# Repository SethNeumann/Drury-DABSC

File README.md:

# REPO NAME: Drury-DABSC
## License: Creative Commons Attribution-NonCommercial-ShareAlike

Dennis Drury designed the Dual ABS Controller (DABSC) as a simple solution for ABS.  
  
The Dual ABS Signal Controller provides a simple, no software, solution for the modeler looking for a prototypical Automatic Block Signaling (ABS) system.
This board provides signal control for two blocks of 3 aspect (Green - Yellow - Red) route signaling for two blocks.  
The Dual ABS Signal Controller can be used in either single track (1 segment for each signaled direction) or double track (Rule 251, Current of Traffic)
applications.

This is an excellent product for modular and sectional railroads as well as permanent applications.  We recommend our cpOD (screw terminal option) detector
for detection input. The Dual ABS Signal Controller is NOT MSS compatible.

This board is designed and supported by Dennis Drury, a former Southern Pacific Signal Maintainer and the design has given him good service for 30 years!
See Dennis' clinic from the 2017 PCR Convention on the development of this board on the www.modelrailroadcontrolsystems.com sitte under Simple Signaling 
and accessories

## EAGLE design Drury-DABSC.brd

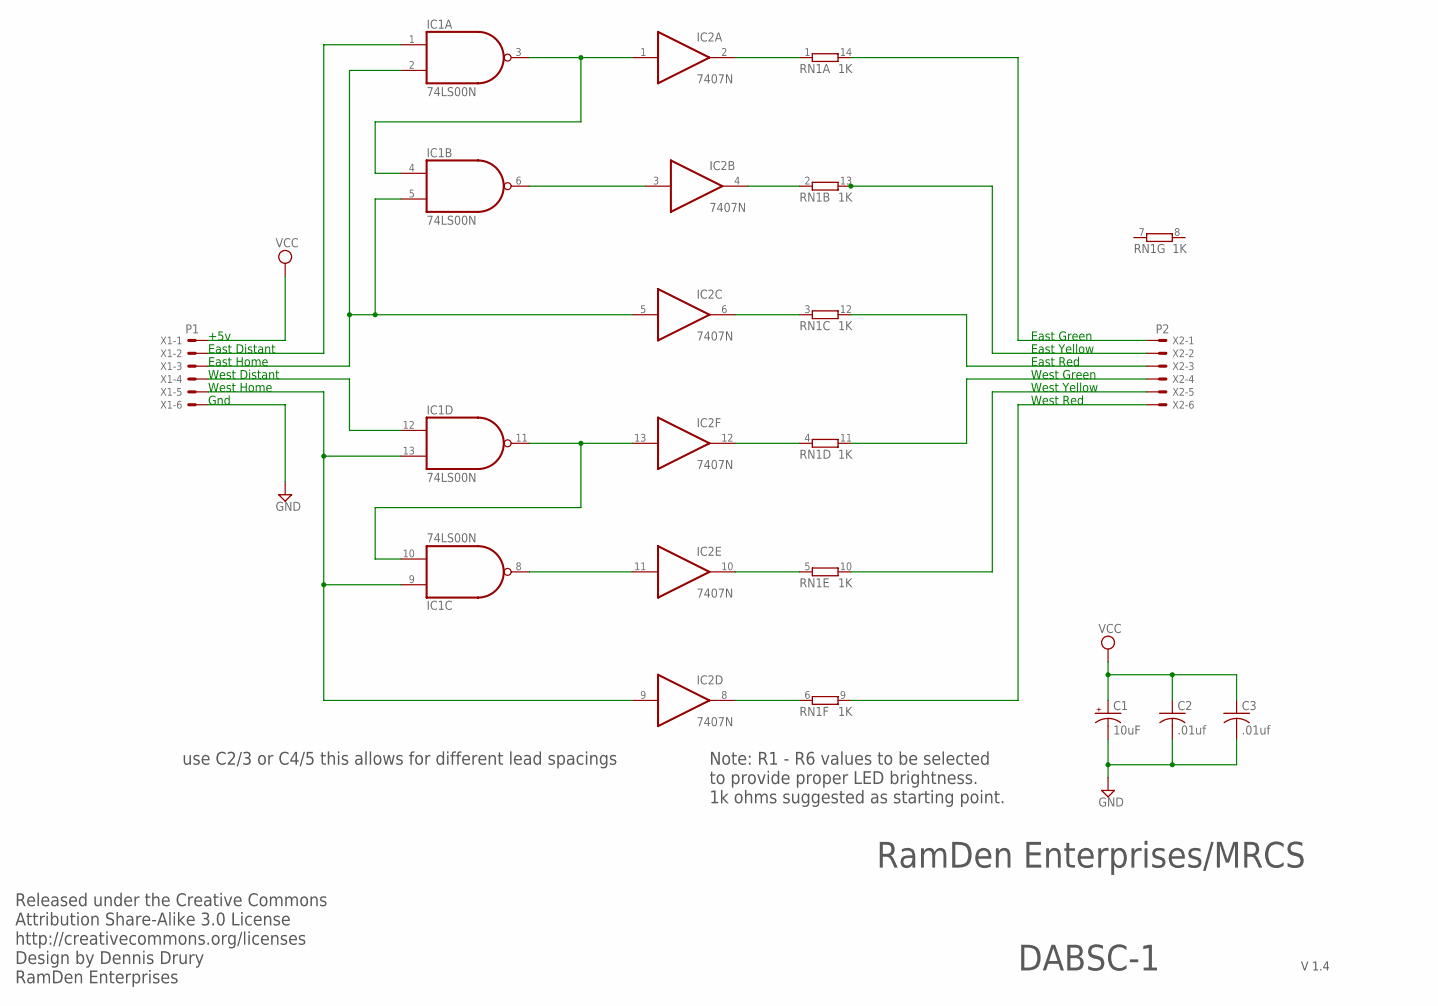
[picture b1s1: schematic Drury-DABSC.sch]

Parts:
C1: 10uF; E2-5
C2, C3: .01uf; C050-025X075
IC1: 74LS00N; DIL14
IC2: 7407N; DIL14
RN1: 1K; DIL14
X1: P1; 22-23-2061
X2: P2; 22-23-2061

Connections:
GND: C1.-, C2.2, C3.2, IC1.7 (GND), IC2.7 (GND), X1.6
unnamed: IC1.3 (O), IC1.4 (I0), IC2.1 (I)
unnamed: IC1.6 (O), IC2.3 (I)
unnamed: IC2.2 (O), RN1.1
unnamed: IC1.8 (O), IC2.11 (I)
unnamed: IC2.4 (O), RN1.2 (1)
unnamed: IC1.10 (I1), IC1.11 (O), IC2.13 (I)
unnamed: IC2.6 (O), RN1.3 (1)
unnamed: RN1.14 (2), X2.1
unnamed: RN1.13 (2), X2.2
unnamed: IC1.1 (I0), X1.2
unnamed: IC1.2 (I1), IC1.5 (I1), IC2.5 (I), X1.3
unnamed: RN1.12 (2), X2.3
unnamed: IC2.12 (O), RN1.4 (1)
unnamed: IC2.10 (O), RN1.5 (1)
unnamed: IC2.8 (O), RN1.6 (1)
unnamed: RN1.9 (2), X2.6
unnamed: RN1.10 (2), X2.5
unnamed: IC1.12 (I0), X1.4
unnamed: RN1.11 (2), X2.4
unnamed: IC1.9 (I0), IC1.13 (I1), IC2.9 (I), X1.5
VCC: C1.+, C2.1, C3.1, IC1.14 (VCC), IC2.14 (VCC), X1.1

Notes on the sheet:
RamDen Enterprises/MRCS
V 1.4
DABSC-1
East Distant
East Home
West Home
West Distant
East Green
East Yellow
East Red
West Green
West Yellow
West Red
Released under the Creative Commons Attribution Share-Alike 3.0 License http://creativecommons.org/licenses Design by Dennis Drury RamDen Enterprises
Note: R1 - R6 values to be selected to provide proper LED brightness. 1k ohms suggested as starting point.
+5v
Gnd
use C2/3 or C4/5 this allows for different lead spacings

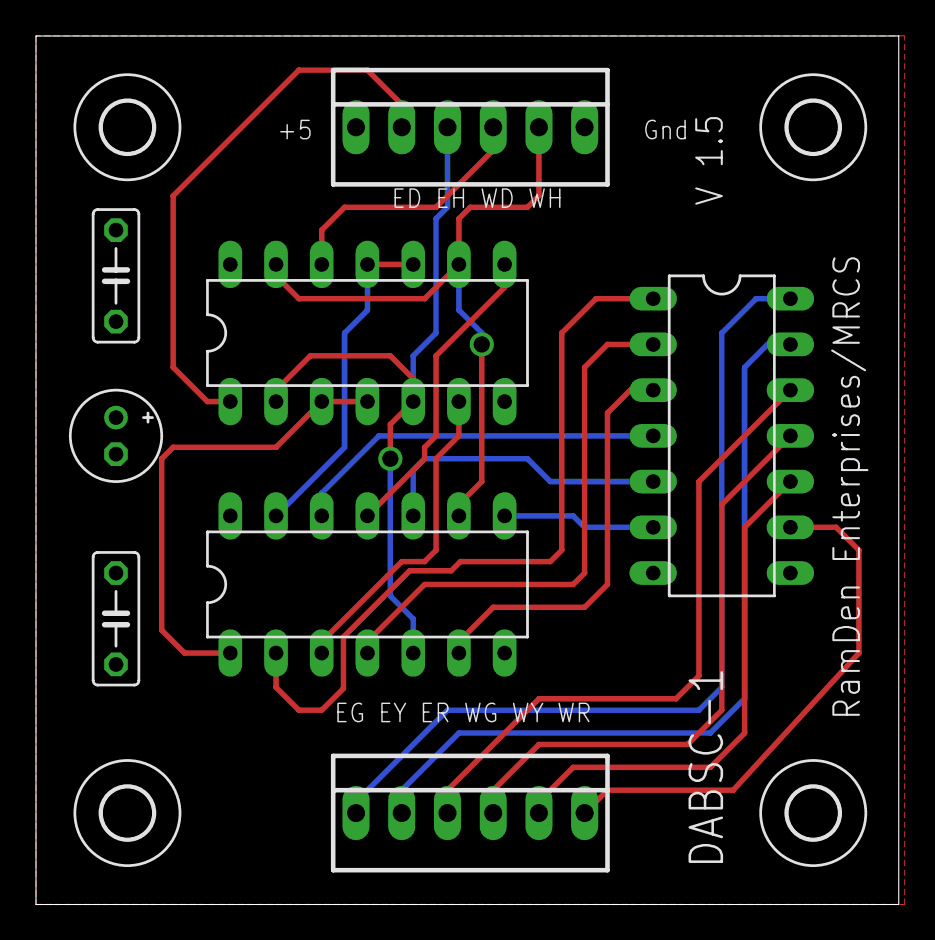
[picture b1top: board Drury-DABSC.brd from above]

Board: 2 copper layers, 47.9 x 48.2 mm, 14 parts (0 on the bottom side), 22 nets.

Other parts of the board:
U$1, U$2, U$3, U$4: 2,8
U$5: MRCSLOGOTOP
U$6: CA-PROP65WARNING

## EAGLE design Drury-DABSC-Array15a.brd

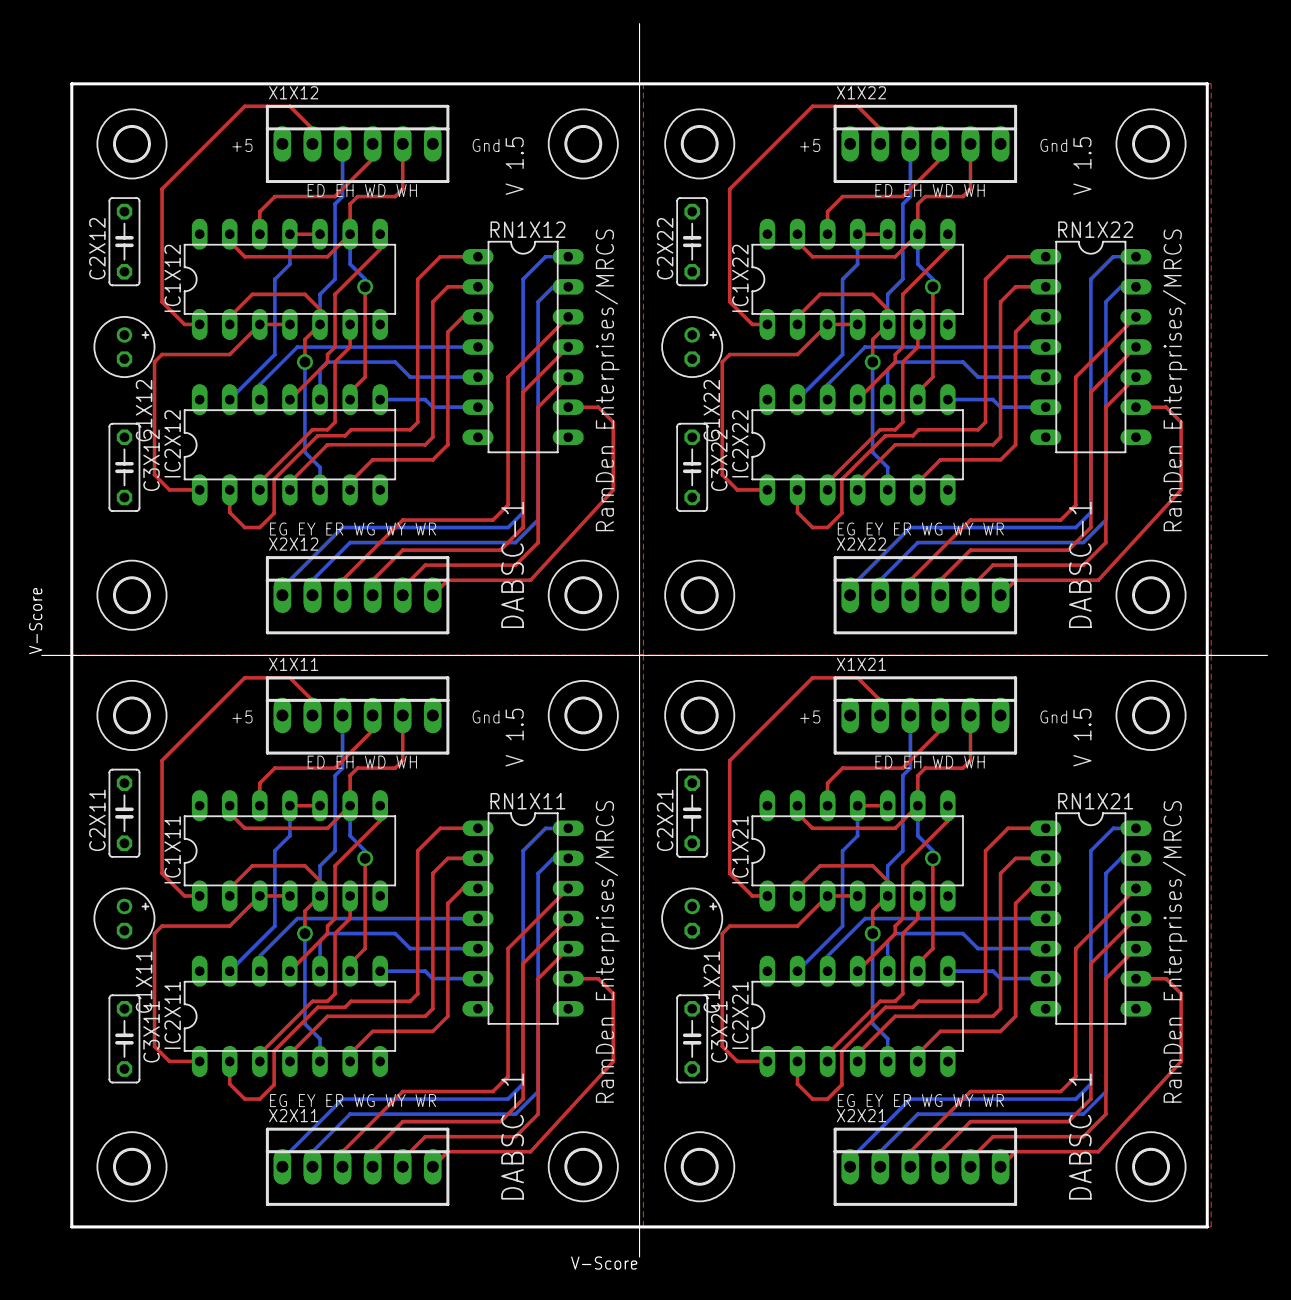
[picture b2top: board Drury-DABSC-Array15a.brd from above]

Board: 2 copper layers, 103.5 x 104.1 mm, 56 parts (0 on the bottom side), 88 nets.

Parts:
C1X11, C1X12, C1X21, C1X22: 10uF; E2-5
C2X11, C2X12, C2X21, C2X22, C3X11, C3X12, C3X21, C3X22: .01uf; C050-025X075
IC1X11, IC1X12, IC1X21, IC1X22: 74LS00N; DIL14
IC2X11, IC2X12, IC2X21, IC2X22: 7407N; DIL14
RN1X11, RN1X12, RN1X21, RN1X22: 1K; DIL14
U$1X11, U$1X12, U$1X21, U$1X22, U$2X11, U$2X12, U$2X21, U$2X22, U$3X11, U$3X12, U$3X21, U$3X22, U$4X11, U$4X12, U$4X21, U$4X22: 2,8
U$5X11, U$5X12, U$5X21, U$5X22: MRCSLOGOTOP
U$6X11, U$6X12, U$6X21, U$6X22: CA-PROP65WARNING
X1X11, X1X12, X1X21, X1X22: P1; 22-23-2061
X2X11, X2X12, X2X21, X2X22: P2; 22-23-2061

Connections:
GNDX11: C1X11.-, C2X11.2, C3X11.2, IC1X11.7, IC2X11.7, X1X11.6
GNDX12: C1X12.-, C2X12.2, C3X12.2, IC1X12.7, IC2X12.7, X1X12.6
GNDX21: C1X21.-, C2X21.2, C3X21.2, IC1X21.7, IC2X21.7, X1X21.6
GNDX22: C1X22.-, C2X22.2, C3X22.2, IC1X22.7, IC2X22.7, X1X22.6
unnamed: IC1X11.3, IC1X11.4, IC2X11.1
unnamed: IC1X12.3, IC1X12.4, IC2X12.1
unnamed: IC1X21.3, IC1X21.4, IC2X21.1
unnamed: IC1X22.3, IC1X22.4, IC2X22.1
unnamed: IC1X11.6, IC2X11.3
unnamed: IC1X12.6, IC2X12.3
unnamed: IC1X21.6, IC2X21.3
unnamed: IC1X22.6, IC2X22.3
unnamed: IC2X11.2, RN1X11.1
unnamed: IC2X12.2, RN1X12.1
unnamed: IC2X21.2, RN1X21.1
unnamed: IC2X22.2, RN1X22.1
unnamed: IC1X11.8, IC2X11.11
unnamed: IC1X12.8, IC2X12.11
unnamed: IC1X21.8, IC2X21.11
unnamed: IC1X22.8, IC2X22.11
unnamed: IC2X11.4, RN1X11.2
unnamed: IC2X12.4, RN1X12.2
unnamed: IC2X21.4, RN1X21.2
unnamed: IC2X22.4, RN1X22.2
unnamed: IC1X11.10, IC1X11.11, IC2X11.13
unnamed: IC1X12.10, IC1X12.11, IC2X12.13
unnamed: IC1X21.10, IC1X21.11, IC2X21.13
unnamed: IC1X22.10, IC1X22.11, IC2X22.13
unnamed: IC2X11.6, RN1X11.3
unnamed: IC2X12.6, RN1X12.3
unnamed: IC2X21.6, RN1X21.3
unnamed: IC2X22.6, RN1X22.3
unnamed: RN1X11.14, X2X11.1
unnamed: RN1X12.14, X2X12.1
unnamed: RN1X21.14, X2X21.1
unnamed: RN1X22.14, X2X22.1
unnamed: RN1X11.13, X2X11.2
unnamed: RN1X12.13, X2X12.2
unnamed: RN1X21.13, X2X21.2
unnamed: RN1X22.13, X2X22.2
unnamed: IC1X11.1, X1X11.2
unnamed: IC1X12.1, X1X12.2
unnamed: IC1X21.1, X1X21.2
unnamed: IC1X22.1, X1X22.2
unnamed: IC1X11.2, IC1X11.5, IC2X11.5, X1X11.3
unnamed: IC1X12.2, IC1X12.5, IC2X12.5, X1X12.3
unnamed: IC1X21.2, IC1X21.5, IC2X21.5, X1X21.3
unnamed: IC1X22.2, IC1X22.5, IC2X22.5, X1X22.3
unnamed: RN1X11.12, X2X11.3
unnamed: RN1X12.12, X2X12.3
unnamed: RN1X21.12, X2X21.3
unnamed: RN1X22.12, X2X22.3
unnamed: IC2X11.12, RN1X11.4
unnamed: IC2X12.12, RN1X12.4
unnamed: IC2X21.12, RN1X21.4
unnamed: IC2X22.12, RN1X22.4
unnamed: IC2X11.10, RN1X11.5
unnamed: IC2X12.10, RN1X12.5
unnamed: IC2X21.10, RN1X21.5
unnamed: IC2X22.10, RN1X22.5
unnamed: IC2X11.8, RN1X11.6
unnamed: IC2X12.8, RN1X12.6
unnamed: IC2X21.8, RN1X21.6
unnamed: IC2X22.8, RN1X22.6
unnamed: RN1X11.9, X2X11.6
unnamed: RN1X12.9, X2X12.6
unnamed: RN1X21.9, X2X21.6
unnamed: RN1X22.9, X2X22.6
unnamed: RN1X11.10, X2X11.5
unnamed: RN1X12.10, X2X12.5
unnamed: RN1X21.10, X2X21.5
unnamed: RN1X22.10, X2X22.5
unnamed: IC1X11.12, X1X11.4
unnamed: IC1X12.12, X1X12.4
unnamed: IC1X21.12, X1X21.4
unnamed: IC1X22.12, X1X22.4
unnamed: RN1X11.11, X2X11.4
unnamed: RN1X12.11, X2X12.4
unnamed: RN1X21.11, X2X21.4
unnamed: RN1X22.11, X2X22.4
unnamed: IC1X11.9, IC1X11.13, IC2X11.9, X1X11.5
unnamed: IC1X12.9, IC1X12.13, IC2X12.9, X1X12.5
unnamed: IC1X21.9, IC1X21.13, IC2X21.9, X1X21.5
unnamed: IC1X22.9, IC1X22.13, IC2X22.9, X1X22.5
VCCX11: C1X11.+, C2X11.1, C3X11.1, IC1X11.14, IC2X11.14, X1X11.1
VCCX12: C1X12.+, C2X12.1, C3X12.1, IC1X12.14, IC2X12.14, X1X12.1
VCCX21: C1X21.+, C2X21.1, C3X21.1, IC1X21.14, IC2X21.14, X1X21.1
VCCX22: C1X22.+, C2X22.1, C3X22.1, IC1X22.14, IC2X22.14, X1X22.1

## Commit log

2022-04-21 intial commit
2022-04-21 imported Dennis's original file as modified by John Plocher
2022-05-07 cleanup of files, labels
    minor fixes for new rev
2022-07-05 changes to support making a panel
    revised board (resistor array, pads for different cap sizes)
2022-11-15 Create DABSC 15 Update.pdf
    describes update, missing label cheat sheet
2022-11-16 changes to labels on terminal blocks
    Changes to labels on terminal blocks. Panelizer not picking them up, they were on Tnames, now on tplace.
2023-08-07 latest version with resistor pack
    Changed to resistor pack to reduce stuffing labor. Use of machined pin socket allows user to insert 1/4W resistors if desired or pick a Bournes 4114 that meets your requirements.
2023-08-08 updated pdf views of V15
    Version 1.5 uses 14 pin DIP for Bournes 4114 style resistor packs
